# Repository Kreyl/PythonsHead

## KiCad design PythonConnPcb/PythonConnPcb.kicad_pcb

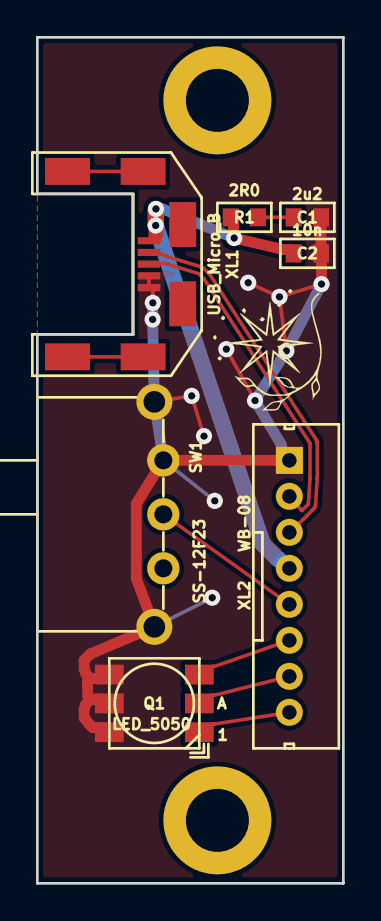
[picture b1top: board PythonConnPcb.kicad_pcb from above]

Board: 2 copper layers, 17.0 x 47.0 mm, 10 parts (0 on the bottom side), 9 nets.

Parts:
C1: 2u2; CAP_0603
C2: 10n; CAP_0603
HOLE1, HOLE2: HOLE_METALLED; Hole3_5_out6mm
Logo1: Logo; Ostranna_8x8
Q1: LED_5050
R1: 2R0; RES_0603
SW1: SS-12F23; SW_SS-12F23
XL1: USB_Micro_B; USBmicro_MOLEX_WM17142
XL2: WB-08; WB-08(MW-8M)

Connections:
/5V: C2.1, R1.1, XL1.1, XL2.4
/B: Q1.1, XL2.8
/D+: XL1.3, XL2.2
/D-: XL1.2, XL2.3
/G: Q1.2, XL2.7
/OnOff: SW1.2, XL2.5
/R: Q1.3, XL2.6
GNDPWR: C1.2, C2.2, Q1.4, Q1.5, Q1.6, SW1.1, SW1.H, XL1.4, XL1.5, XL2.1
unnamed: C1.1, R1.2

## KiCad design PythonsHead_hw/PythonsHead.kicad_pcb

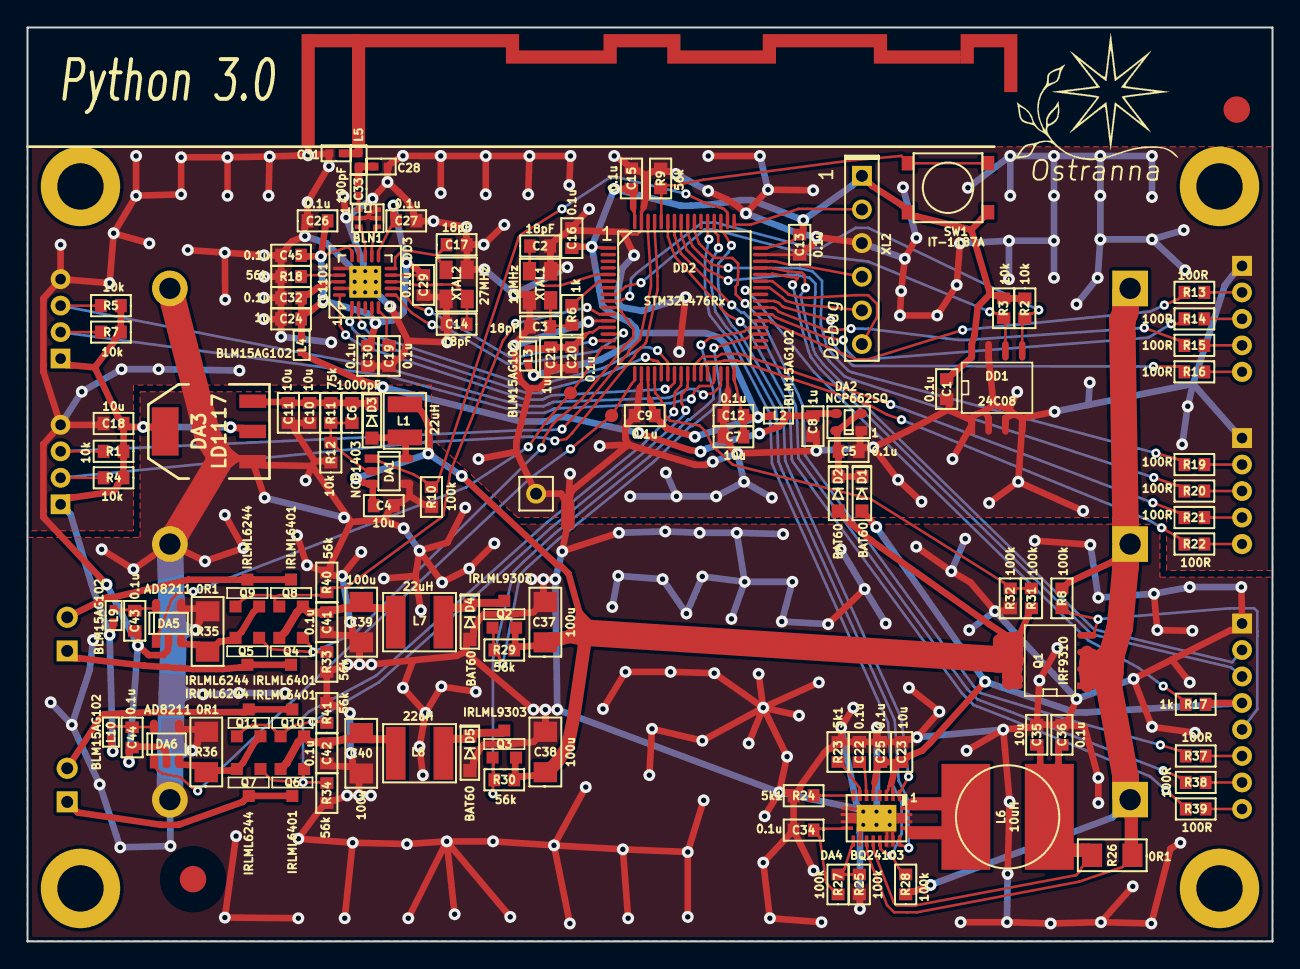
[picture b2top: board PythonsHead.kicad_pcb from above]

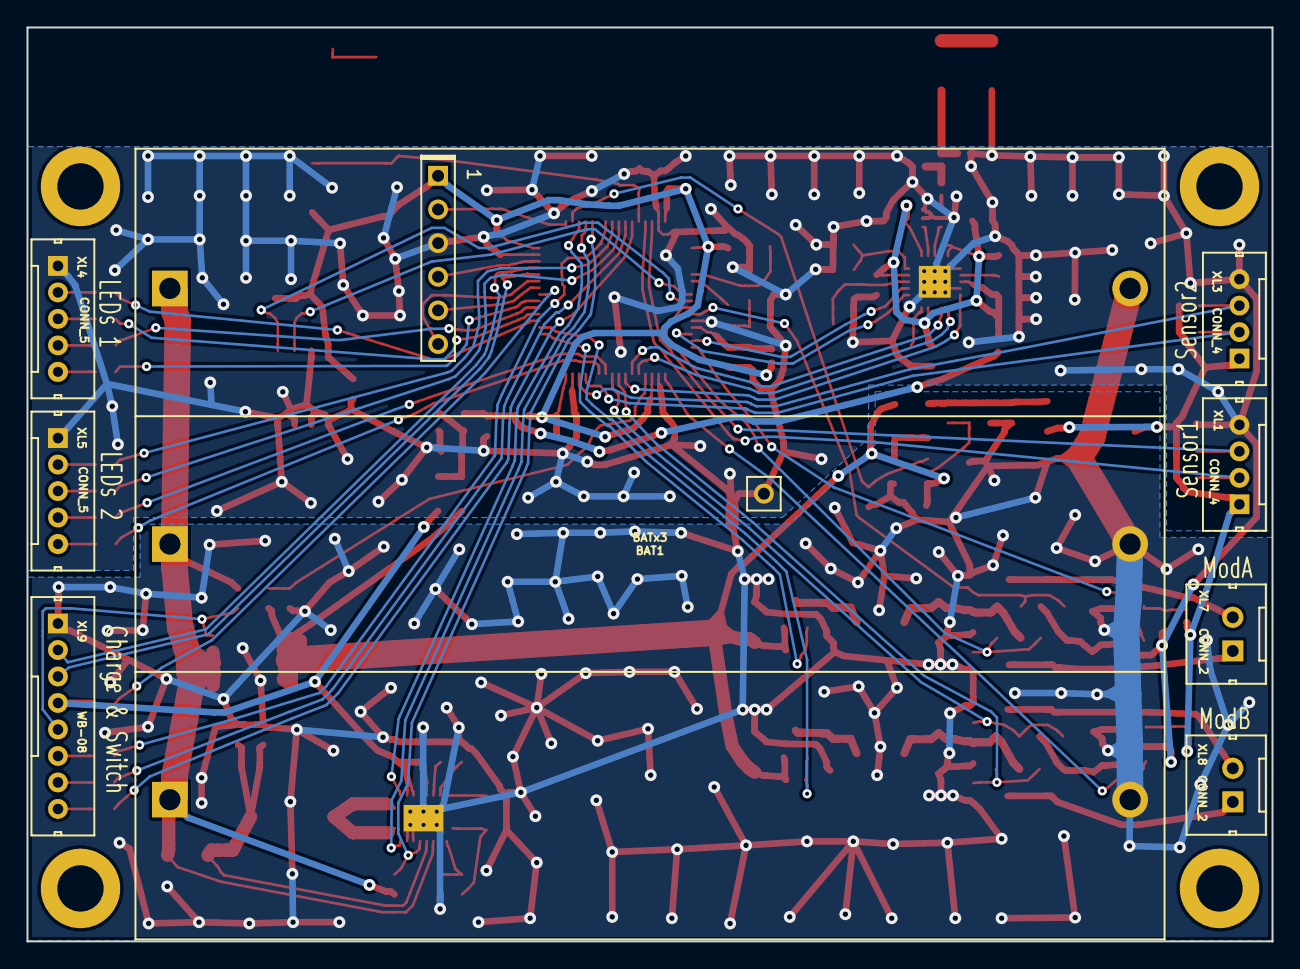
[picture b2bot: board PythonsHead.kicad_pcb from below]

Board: 2 copper layers, 94.0 x 69.0 mm, 146 parts (8 on the bottom side), 100 nets.

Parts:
ANT1: ANT_PCB_MONO_2PIN; ANT_868_IFA_SIMPLEJOY
BAT1: BATx3; 18650x3
BLN1: BALUN868JOHANSON; BALUN_JOHANSON868
C1, C5, C9, C12, C13, C15, C16, C19, C20, C22, C25, C26, C27, C29, C30, C32, C34, C36, C41, C42, C43, C44, C45: 0.1u; CAP_0603
C2, C3, C14, C17: 18pF; CAP_0603
C4, C7, C10, C11, C18, C23, C35: 10u; CAP_0603
C6: 1000pF; CAP_0603
C8, C21, C24: 1u; CAP_0603
C28, C31: *; CAP_0402
C33: 100pF; CAP_0402
C37, C38, C39, C40: 100u; RES_1206
D1, D2, D3, D4, D5: BAT60; SOD323
DA1: NCP1403; SOT23-5
DA2: NCP662SQ; SC82AB
DA3: LD1117; SOT223
DA4: BQ24103; RPVQFN-N20
DA5, DA6: AD8211; SOT23-5
DD1: 24C08; SO8_150MIL
DD2: STM32L476Rx; LQFP64
DD3: CC1101; QFN20
F1: Fuse0R; FuseShorted
HOLE1, HOLE2, HOLE3, HOLE4: HOLE_METALLED; Hole3_5_out6mm
L1: 22uH; IND_1210_LQH32C
L2, L3, L4, L9, L10: BLM15AG102; IND_0402
L5: *; IND_0402
L6: 10uH; SDR0805
L7, L8: 22uH; SRN5040
Logo1: Logo; Ostranna_12d7_10d1
Q1: IRF9310; SO8_150MIL
Q2, Q3: IRLML9303; SOT23-3
Q4, Q6, Q8, Q10: IRLML6401; SOT23-3
Q5, Q7, Q9, Q11: IRLML6244; SOT23-3
R1, R2, R3, R4, R5, R7, R12: 10k; RES_0603
R6, R17: 1k; RES_0603
R8, R10, R25, R27, R28, R31, R32: 100k; RES_0603
R9, R18, R29, R30, R33, R34, R40, R41: 56k; RES_0603
R11: 75k; RES_0603
R13, R14, R15, R16, R19, R20, R21, R22, R37, R38, R39: 100R; RES_0603
R23, R24: 5k1; RES_0603
R26, R35, R36: 0R1; RES_1206
RP1, RP2: REFPOINT; REF_POINT_2MM
SW1: IT-1187A; BTN_4x4_SMD
TP1, TP2: TESTPOINT; TESTPOINT_1MM
XL1, XL3: CONN_4; WB-04(MW-4M)
XL2: CONN_6; PLS-6
XL4, XL5: CONN_5; WB-05(MW-5M)
XL6: CONN_1; PLS-1Rnd
XL7, XL8: CONN_2; W02_Pitch_2d54
XL9: WB-08; WB-08(MW-8M)
XTAL1: 12MHz; 03225C4
XTAL2: 27MHz; 03225C4

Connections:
+3.3V: C8.1, DA2.3, L2.2, L4.2
+5V: C18.2, DA3.2, DA3.PAD, L9.1, L10.1, R1.1, R4.1, R5.1, R7.1, XL1.1, XL3.1
+BATT: C4.2, C37.1, C38.1, D2.A, DA1.3, L1.2, Q1.5, Q1.6, Q1.7, Q1.8, Q2.2, Q3.2, R29.1, R30.1, R31.1
/5V_EN: DA1.1, DD2.50, R10.2
/5V_USB: C23.2, C25.1, D1.A, DA4.3, DA4.4, DA4.6, R17.2, XL9.4
/ANT1: C28.1, C33.1, L5.2
/ANT2: ANT1.1, C31.1, L5.1
/B: DD2.59, R39.2
/BATTERY: BAT1.1, BAT1.2, BAT1.3, DA4.14, Q1.1, Q1.2, Q1.3, R8.2, R26.1, R28.1
/BAT_MEAS: DD2.20, R31.2, R32.1
/CC_CS: DD2.15, DD3.7
/CC_GDO0: DD2.14, DD3.6
/CC_MISO: DD2.22, DD3.2
/CC_MOSI: DD2.23, DD3.20
/CC_SCK: DD2.21, DD3.1
/CHARGE_EN: DA4.16, DD2.53, R28.2
/D+: DD2.45, XL9.2
/D-: DD2.44, XL9.3
/G: DD2.58, R38.2
/HTRA1: Q4.3, Q5.3, XL7.1
/HTRA2: Q8.3, Q9.3, XL7.2
/HTRA_CURR: DA5.1, DD2.16, TP1.1
/HTRA_DIR1: DD2.10, Q4.1, Q5.1, R33.1
/HTRA_DIR2: DD2.11, Q8.1, Q9.1, R40.1
/HTRA_GND: DA5.3, Q5.2, Q9.2, R35.1
/HTRA_PWM_CTRL: DD2.35, Q2.1, R29.2
/HTRA_PWR: C39.1, C41.2, L7.1, Q4.2, Q8.2
/HTRB1: Q6.3, Q7.3, XL8.1
/HTRB2: Q10.3, Q11.3, XL8.2
/HTRB_CURR: DA6.1, DD2.17, TP2.1
/HTRB_DIR1: DD2.24, Q6.1, Q7.1, R34.1
/HTRB_DIR2: DD2.25, Q10.1, Q11.1, R41.1
/HTRB_GND: DA6.3, Q7.2, Q11.2, R36.1
/HTRB_PWM_CTRL: DD2.36, Q3.1, R30.2
/HTRB_PWR: C40.1, C42.2, L8.1, Q6.2, Q10.2
/LED1_PWM_CTRL: DD2.37, R13.2
/LED2_PWM_CTRL: DD2.38, R14.2
/LED3_PWM_CTRL: DD2.39, R15.2
/LED4_PWM_CTRL: DD2.40, R16.2
/LED5_PWM_CTRL: DD2.56, R19.2
/LED6_PWM_CTRL: DD2.57, R20.2
/LED7_PWM_CTRL: DD2.26, R21.2
/LED8_PWM_CTRL: DD2.27, R22.2
/OnOff: Q1.4, R8.1, XL9.5
/PWR_LX: D3.A, DA1.5, L1.1
/PWR_MID: C6.2, C10.2, C11.2, D3.C, DA3.3, R11.2
/R: DD2.55, R37.2
/RF1: BLN1.4, DD3.12
/RF2: BLN1.3, DD3.13
/SCL_EE: DD1.6, DD2.8, R3.1
/SCL_SNS1: DD2.61, R4.2, XL1.2
/SCL_SNS2: DD2.29, R7.2, XL3.2
/SDA_EE: DD1.5, DD2.9, R2.2
/SDA_SNS1: DD2.62, R1.2, XL1.3
/SDA_SNS2: DD2.30, R5.2, XL3.3
/STAT1: DA4.2, DD2.51
/STAT2: DA4.19, DD2.52
/SWCLK: DD2.49, XL2.2
/SWDIO: DD2.46, XL2.4
/UART_RX: DD2.43, XL2.6
/UART_TX: DD2.42, XL2.5
/VDDA: C20.2, C21.2, DD2.13, L3.1
/VTSB: C34.1, DA4.11, R27.1
GND: ANT1.2, BLN1.2, BLN1.5, BLN1.6, C1.1, C2.2, C3.2, C5.2, C7.1, C8.2, C9.1, C12.1, C13.1, C14.2, C15.1, C16.1, C17.2, C18.1, C19.1, C20.1, C21.1, C24.1, C26.1, C27.1, C28.2, C29.1, C30.1, C31.2, C32.1, C43.1, C44.1, C45.1, DA2.1, DA5.2, DA6.2, DD1.1, DD1.2, DD1.3, DD1.4, DD1.7, DD2.12, DD2.18, DD2.31, DD2.47, DD2.63, DD3.16, DD3.19, DD3.PAD, F1.1, R9.2, R18.2, XL1.4, XL2.3, XL3.4, XL4.1, XL5.1, XL6.1, XTAL1.H, XTAL2.H
GNDPWR: BAT1.4, BAT1.5, BAT1.6, C4.1, C10.1, C11.1, C22.2, C23.1, C25.2, C34.2, C35.1, C36.2, C37.2, C38.2, C39.2, C40.2, C41.1, C42.1, D4.A, D5.A, DA1.4, DA3.1, DA4.10, DA4.13, DA4.17, DA4.18, DA4.PAD, DA5.4, DA6.4, F1.2, R10.1, R12.1, R23.1, R24.1, R25.2, R32.2, R33.2, R34.2, R35.2, R36.2, R40.2, R41.2, XL9.1
unnamed: BLN1.1, C33.2
unnamed: C2.1, DD2.5, XTAL1.1
unnamed: C3.1, R6.1, XTAL1.2
unnamed: C5.1, D1.C, D2.C, DA2.2, DA2.4
unnamed: C6.1, DA1.2, R11.1, R12.2
unnamed: C14.1, DD3.8, XTAL2.1
unnamed: C17.1, DD3.10, XTAL2.2
unnamed: C19.2, DD3.5
unnamed: C22.1, DA4.7
unnamed: C35.2, C36.1, DA4.15, L6.1, R26.2
unnamed: C43.2, DA5.5, L9.2
unnamed: C44.2, DA6.5, L10.2
unnamed: D4.C, L7.2, Q2.3
unnamed: D5.C, L8.2, Q3.3
unnamed: DA4.1, DA4.20, L6.2
unnamed: DA4.8, R23.2
unnamed: DA4.9, R24.2
unnamed: DA4.12, R25.1, R27.2
unnamed: DD2.6, R6.2
unnamed: DD2.41, R17.1
unnamed: DD2.60, R9.1, SW1.1
unnamed: DD3.17, R18.1
unnamed: R13.1, XL4.2
unnamed: R14.1, XL4.3
unnamed: R15.1, XL4.4
unnamed: R16.1, XL4.5
unnamed: R19.1, XL5.2
unnamed: R20.1, XL5.3
unnamed: R21.1, XL5.4
unnamed: R22.1, XL5.5
unnamed: R37.1, XL9.6
unnamed: R38.1, XL9.7
unnamed: R39.1, XL9.8
PwrMCU: C1.2, C7.2, C9.2, C12.2, C13.2, C15.2, C16.2, DD1.8, DD2.1, DD2.19, DD2.32, DD2.48, DD2.64, L2.1, L3.2, R2.1, R3.2, SW1.2, XL2.1
VCC: C24.2, C26.2, C27.2, C29.2, C30.2, C32.2, C45.2, DD3.4, DD3.9, DD3.11, DD3.14, DD3.15, DD3.18, L4.1

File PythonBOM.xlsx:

Reference | Value | Footprint | Quantity | URL | Price | SolderPoints | PN | Icc | Sum
ANT1 | ANT_PCB_MONO_2PIN | Radio:ANT_868_IFA_SIMPLEJOY | 1 |  | 0 | 0
BAT1 | BATx3 | Installation:18650x3 | 1 | http://www.quartz1.com/price/model.php?akt=9419.16 | 350 | 6 |  |  |  | Заказано
BLN1 | BALUN868JOHANSON | Radio:BALUN_JOHANSON868 | 1 | http://onelec.ru/products/0896bm15a0001e-52ab3408-7c12-4b8c-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 |  | 6 | 0896BM15A0001E
C1 C12 C13 C15 C16 C19 C20 C22 C25 C26 C27 C29 C30 C32 C34 C36 C41 C42 C43 C44 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 | 0.1u | Capacitors:CAP_0603 | 23 |  | 0.5 | 2
C14 C17 C2 C3 | 18pF | Capacitors:CAP_0603 | 4 |  | 0.5 | 2
C28 C31 | * | Capacitors:CAP_0402 | 2 |  | 0.5 | 2
C33 | 100pF | Capacitors:CAP_0402 | 1 |  | 0 | 0
C37 C38 C39 C40 | 100u | Resistors:RES_1206 | 4 | https://www.terraelectronica.ru/product/877677 | 13 | 2 | CL31A107MQHNNNE
C6 | 1000pF | Capacitors:CAP_0603 | 1 | https://www.terraelectronica.ru/catalog.php?ID=1155&search=c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 | 2.5 | 2 | CL10A106MQ8NNNC
C10 C11 C18 C23 C35 C4 C7 | 10u | Capacitors:CAP_0603 | 7 | https://www.terraelectronica.ru/catalog.php?ID=1155&search=c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 | 2.5 | 2 | CL10A106MQ8NNNC
C21 C24 C8 | 1u | Capacitors:CAP_0603 | 3 |  | 0.5 | 2
D1 D2 D3 D4 D5 | BAT60 | Diodes:SOD323 | 5 | https://www.terraelectronica.ru/product/446448 | 6 | 2 | BAT60JFILM
DA1 | NCP1403 | SOT:SOT23-5 | 1 |  | 28 | 5 | NCP1403SNT1G
DA2 | NCP662SQ | SOT:SC82AB | 1
DA3 | LD1117 | SOT:SOT223 | 1 | http://onelec.ru/products/ncp1117st50t3g-9f0c534c-f7a1-467d-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 | 13 | 4 | NCP1117ST50T3G
DA4 | BQ24103 | QFN_DFN:RPVQFN-N20 | 1 |  | 217 | 21 | BQ24103ARHLT
DA5 DA6 | AD8211 | SOT:SOT23-5 | 2 |  | 110 | 5
DD1 | 24C08 | SO_DIL_TSSOP:SO8_150MIL | 1 | https://www.terraelectronica.ru/catalog_info.php?CODE=328439 | 8.5 | 8 | M24C08-WMN6P | 1
DD2 | STM32L476Rx | LQFP_TQFP:LQFP64 | 1 |  | 290 | 64 | STM32L476RCT6
DD3 | CC1101 | QFN_DFN:QFN20 | 1 | http:// | 140 | 21
F1 | Fuse0R | PCB:FuseShorted | 1 |  | 0 | 0
HOLE1 HOLE2 HOLE3 HOLE4 | HOLE_METALLED | PCB:Hole3_5_out6mm | 4 |  | 0 | 0
L1 | 22uH | Inductors:IND_1210_LQH32C | 1 |  | 4 | 2
L10 L2 L3 L4 L9 | BLM15AG102 | Inductors:IND_0402 | 5 |  | 1 | 2 | BLM15AG102SN1
L5 | * | Inductors:IND_0402 | 1 |  | 4 | 2
L6 | 10uH | Inductors:SDR0805 | 1 | https://www.terraelectronica.ru/product/217833 | 22 | 2 | SDR0805-100ML
L7 L8 | 22uH | Inductors:SRN5040 | 2 |  | 15 | 2 | SRN5040-220M
Logo1 | Logo | Pictures:Ostranna_12d7_10d1 | 1 |  | 0 | 0
Q1 | IRF9310 | SO_DIL_TSSOP:SO8_150MIL | 1
Q2 Q3 | IRLML9303 | SOT:SOT23-3 | 2 |  |  | 3 |  |  |  | Купить штук 200
Q10 Q4 Q6 Q8 | IRLML6401 | SOT:SOT23-3 | 4 |  |  | 3
Q11 Q5 Q7 Q9 | IRLML6244 | SOT:SOT23-3 | 4 |  | 5.5 | 3
R1 R12 R2 R3 R4 R5 R7 | 10k | Resistors:RES_0603 | 7
R11 | 75k | Resistors:RES_0603 | 1 |  | 0.5 | 2
R13 R14 R15 R16 R19 R20 R21 R22 R37 R38 R39 | 100R | Resistors:RES_0603 | 11 |  | 0.5 | 2
R18 R29 R30 R33 R34 R40 R41 R9 | 56k | Resistors:RES_0603 | 8 |  | 0.5 | 2
R23 R24 | 5k1 | Resistors:RES_0603 | 2 |  | 0.5 | 2 |  |  |  | Купить 100шт
R10 R25 R27 R28 R31 R32 R8 | 100k | Resistors:RES_0603 | 7 |  | 0.5 | 2
R26 R35 R36 | 0R1 | Resistors:RES_1206 | 3 |  | 0.5 | 2
R17 R6 | 1k | Resistors:RES_0603 | 2 |  | 0.5 | 2
RP1 RP2 | REFPOINT | PCB:REF_POINT_2MM | 2 |  | 0 | 0
SW1 | IT-1187A | BtnsSwitches:BTN_4x4_SMD | 1 | http://www.zip-2002.ru/kommutatsiya/taktovye_knopki/83335/it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 | 4 | 4
TP1 TP2 | TESTPOINT | PCB:TESTPOINT_1MM | 2 |  | 0 | 0
XL1 XL3 | CONN_4 | Connectors:WB-04(MW-4M) | 2
XL2 | CONN_6 | Connectors:PLS-6 | 1 |  | 2 | 6
XL4 XL5 | CONN_5 | Connectors:WB-05(MW-5M) | 2 | http://www.brownbear.ru/goods/5149.html | 3 | 5 |  |  |  | Купить 100шт
XL6 | CONN_1 | Connectors:PLS-1Rnd | 1 |  | 0 | 0
XL7 XL8 | CONN_2 | Connectors:W02_Pitch_2d54 | 2
XL9 | WB-08 | Connectors:WB-08(MW-8M) | 1 | http://www.zip-2002.ru/razyemy/razyemy_pitaniya_nizkovoltnye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 | 2
XTAL1 | 12MHz | Quartz:03225C4 | 1 | http://www.quartz1.com/price/model.php?akt=3833.12 | 15 | 4
XTAL2 | 27MHz | Quartz:03225C4 | 1 |  | 15 | 4

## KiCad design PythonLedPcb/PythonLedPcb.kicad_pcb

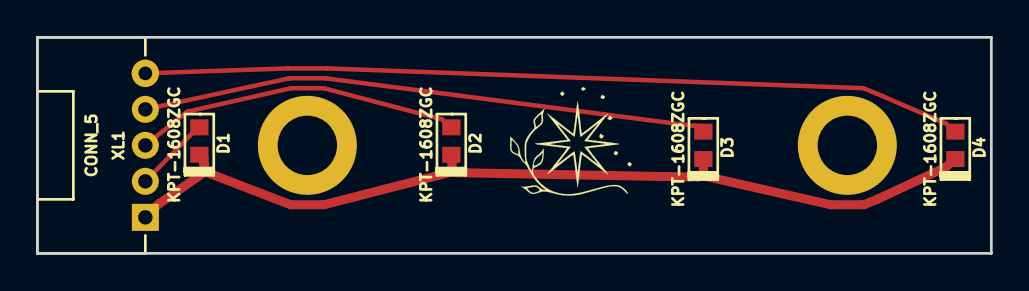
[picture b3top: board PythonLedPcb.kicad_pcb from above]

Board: 2 copper layers, 53.0 x 12.0 mm, 8 parts (0 on the bottom side), 5 nets.

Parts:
D1, D2, D3, D4: KPT-1608ZGC; LED_0603
HOLE1, HOLE2: HOLE_METALLED; Hole3d3_out5d5mm
Logo1: Logo; Ostranna_8x8
XL1: CONN_5; WB-05R(MW-5MR)

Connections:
unnamed: D1.A, XL1.2
unnamed: D1.C, D2.C, D3.C, D4.C, XL1.1
unnamed: D2.A, XL1.3
unnamed: D3.A, XL1.4
unnamed: D4.A, XL1.5

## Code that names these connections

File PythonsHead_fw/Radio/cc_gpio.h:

/*
 * cc_gpio.h
 *
 *  Created on: Nov 28, 2013
 *      Author: kreyl
 */

#pragma once

// Pins
#define CC_GPIO     GPIOA
#define CC_GDO2     2
#define CC_GDO0     3
#define CC_SCK      5
#define CC_MISO     6
#define CC_MOSI     7
#define CC_CS       1

#if defined STM32L1XX
    #if CC_GDO0 == 0
    #define GDO0_IRQ_HANDLER     Vector58
    #elif CC_GDO0 == 1
    #define GDO0_IRQ_HANDLER     Vector5C
    #elif CC_GDO0 == 2
    #define GDO0_IRQ_HANDLER     Vector60
    #elif CC_GDO0 == 3
    #define GDO0_IRQ_HANDLER     Vector64
    #elif CC_GDO0 == 4
    #define GDO0_IRQ_HANDLER     Vector68
    #endif

#elif defined STM32F072xB
    #if (CC_GDO0 == 0) || (CC_GDO0 == 1)
    #define GDO0_IRQ_HANDLER     Vector54
    #elif (CC_GDO0 == 2) || (CC_GDO0 == 3)
    #define GDO0_IRQ_HANDLER     Vector58
    #else
    #define GDO0_IRQ_HANDLER     Vector5C
    #endif
#endif

// SPI
#define CC_SPI      SPI1
#if defined STM32L1XX
#define CC_SPI_AF   AF5
#elif defined STM32F030 || defined STM32F072xB
#define CC_SPI_AF   AF0
#endif

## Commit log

2016-01-23 + PCB routed, but still no antenna
2016-01-23 * Topor files changed
2016-02-09 * HW done + FW radio init
2016-02-09 + Sns + Radio ok
2016-02-10 alpha
2016-12-19 + Control sw
2016-12-19 + sw
2016-12-19 Nearly everything works
2016-12-20 Middle of refactoring
2016-12-20 Refactoring done
2016-12-20 Temperatures transmission ok
2016-12-20 Param reception ok
2016-12-20 Freq implemented, but not works
2016-12-20 + "SendAll" btn + freq control
2017-03-01 L476
2017-03-02 Before switch to F205
2017-03-02 Proceeding with sch
2017-03-02 Proceeding
2017-03-03 Layout done
2017-03-04 sent to fabric
2017-04-06 Python2 FW hello world
2017-04-06 Fighting with LEDs
2017-04-07 + Peltye control works ok Laucaringi
2017-04-07 + ADC works + Mediana sorting
2017-04-07 Antenna matched
2017-04-14 + Adjust by millivolts
2017-04-15 + Settings work
2017-04-15 + Radio works
2017-04-15 + Sns works
2017-04-16 + Settings save/load
2017-04-16 Settings save/load
2017-04-16 + GetParams from python
2017-05-04 + LedPCB
2017-10-06 Some minor optimizations Disabled Peltye chls 2...6
2018-02-24 + BOM + Block diag
2018-02-24 + Conn PCB (unrouted) + LED PCB (unrouted)
2018-02-26 Proceeding with v3 sch
2018-02-26 SCH done, proceeding with layout
2018-02-27 First version of layout
2018-02-28 V3 sent to factory
2018-04-14 Something
